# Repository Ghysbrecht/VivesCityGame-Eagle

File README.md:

# VivesCityGame-Eagle
Eagle projects for the VivesCityGame project. This includes the board and schematic files for both the main board and the led board.

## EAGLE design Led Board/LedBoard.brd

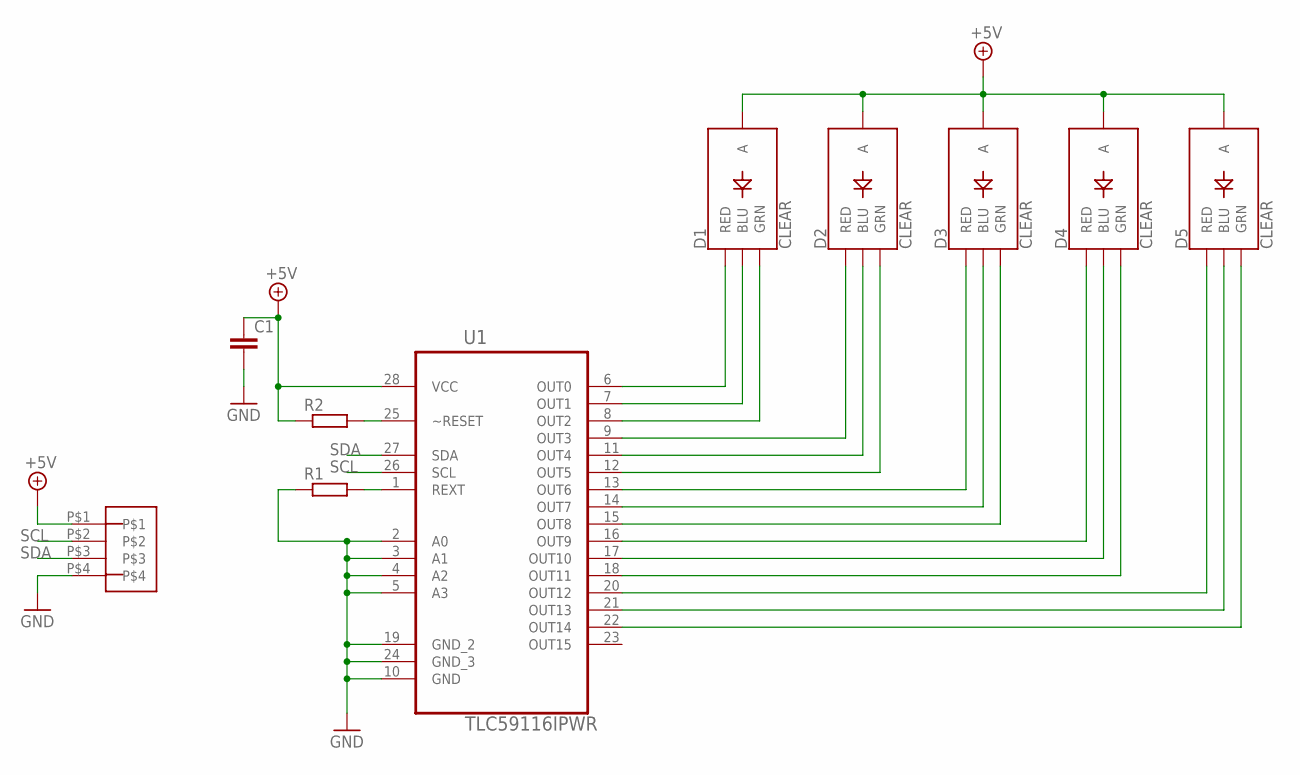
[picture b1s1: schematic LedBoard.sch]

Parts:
C1: C-EUC0603; C0603
D1, D2, D3, D4, D5: CLEAR; LED-RGB-THRU
R1, R2: R-EU_R0603; R0603
U1: TLC59116IPWR; SOP65P640X120-28N
U$1: 4_PIN_JST-XH

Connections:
+5V: C1.1, D1.2 (A), D2.2 (A), D3.2 (A), D4.2 (A), D5.2 (A), R2.1, U1.28 (VCC), U$1.P$1
GND: C1.2, R1.1, U1.2 (A0), U1.3 (A1), U1.4 (A2), U1.5 (A3), U1.10 (GND), U1.19 (GND_2), U1.24 (GND_3), U$1.P$4
unnamed: D1.1 (RED), U1.6 (OUT0)
unnamed: D1.4 (BLU), U1.7 (OUT1)
unnamed: D1.3 (GRN), U1.8 (OUT2)
unnamed: D2.1 (RED), U1.9 (OUT3)
unnamed: D2.4 (BLU), U1.11 (OUT4)
unnamed: D2.3 (GRN), U1.12 (OUT5)
unnamed: D3.1 (RED), U1.13 (OUT6)
unnamed: D3.4 (BLU), U1.14 (OUT7)
unnamed: D3.3 (GRN), U1.15 (OUT8)
unnamed: D4.1 (RED), U1.16 (OUT9)
unnamed: D4.4 (BLU), U1.17 (OUT10)
unnamed: D4.3 (GRN), U1.18 (OUT11)
unnamed: D5.1 (RED), U1.20 (OUT12)
unnamed: D5.4 (BLU), U1.21 (OUT13)
unnamed: D5.3 (GRN), U1.22 (OUT14)
unnamed: R1.2, U1.1 (REXT)
unnamed: R2.2, U1.25 (~RESET)
SCL: U1.26 (SCL), U$1.P$2
SDA: U1.27 (SDA), U$1.P$3

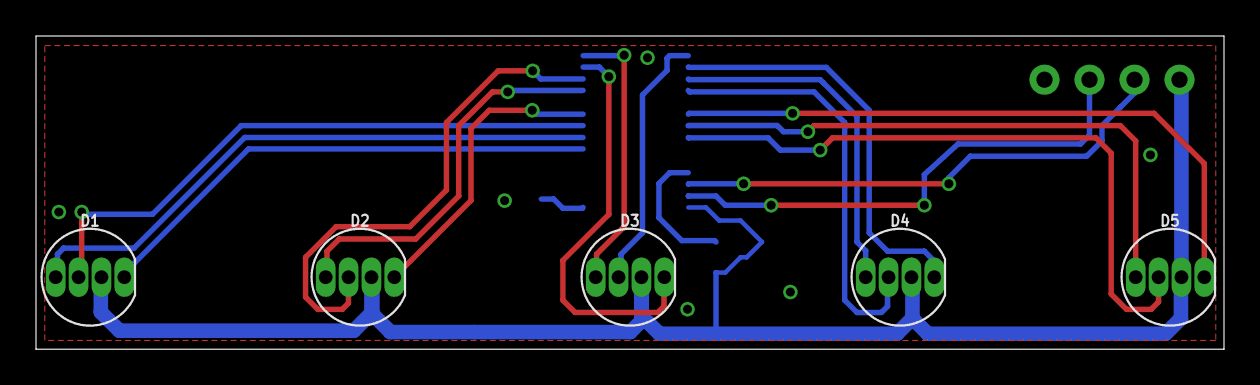
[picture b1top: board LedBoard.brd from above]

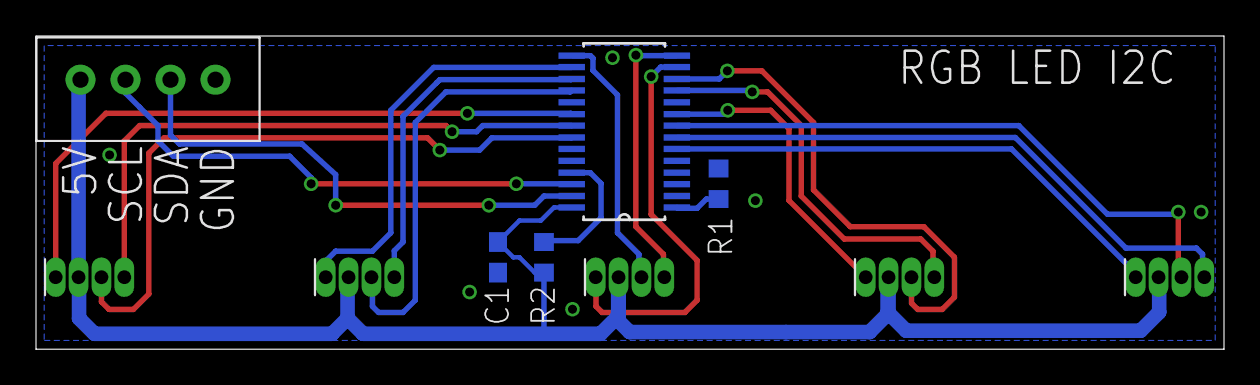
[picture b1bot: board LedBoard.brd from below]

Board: 2 copper layers, 66.0 x 17.4 mm, 10 parts (5 on the bottom side), 21 nets.

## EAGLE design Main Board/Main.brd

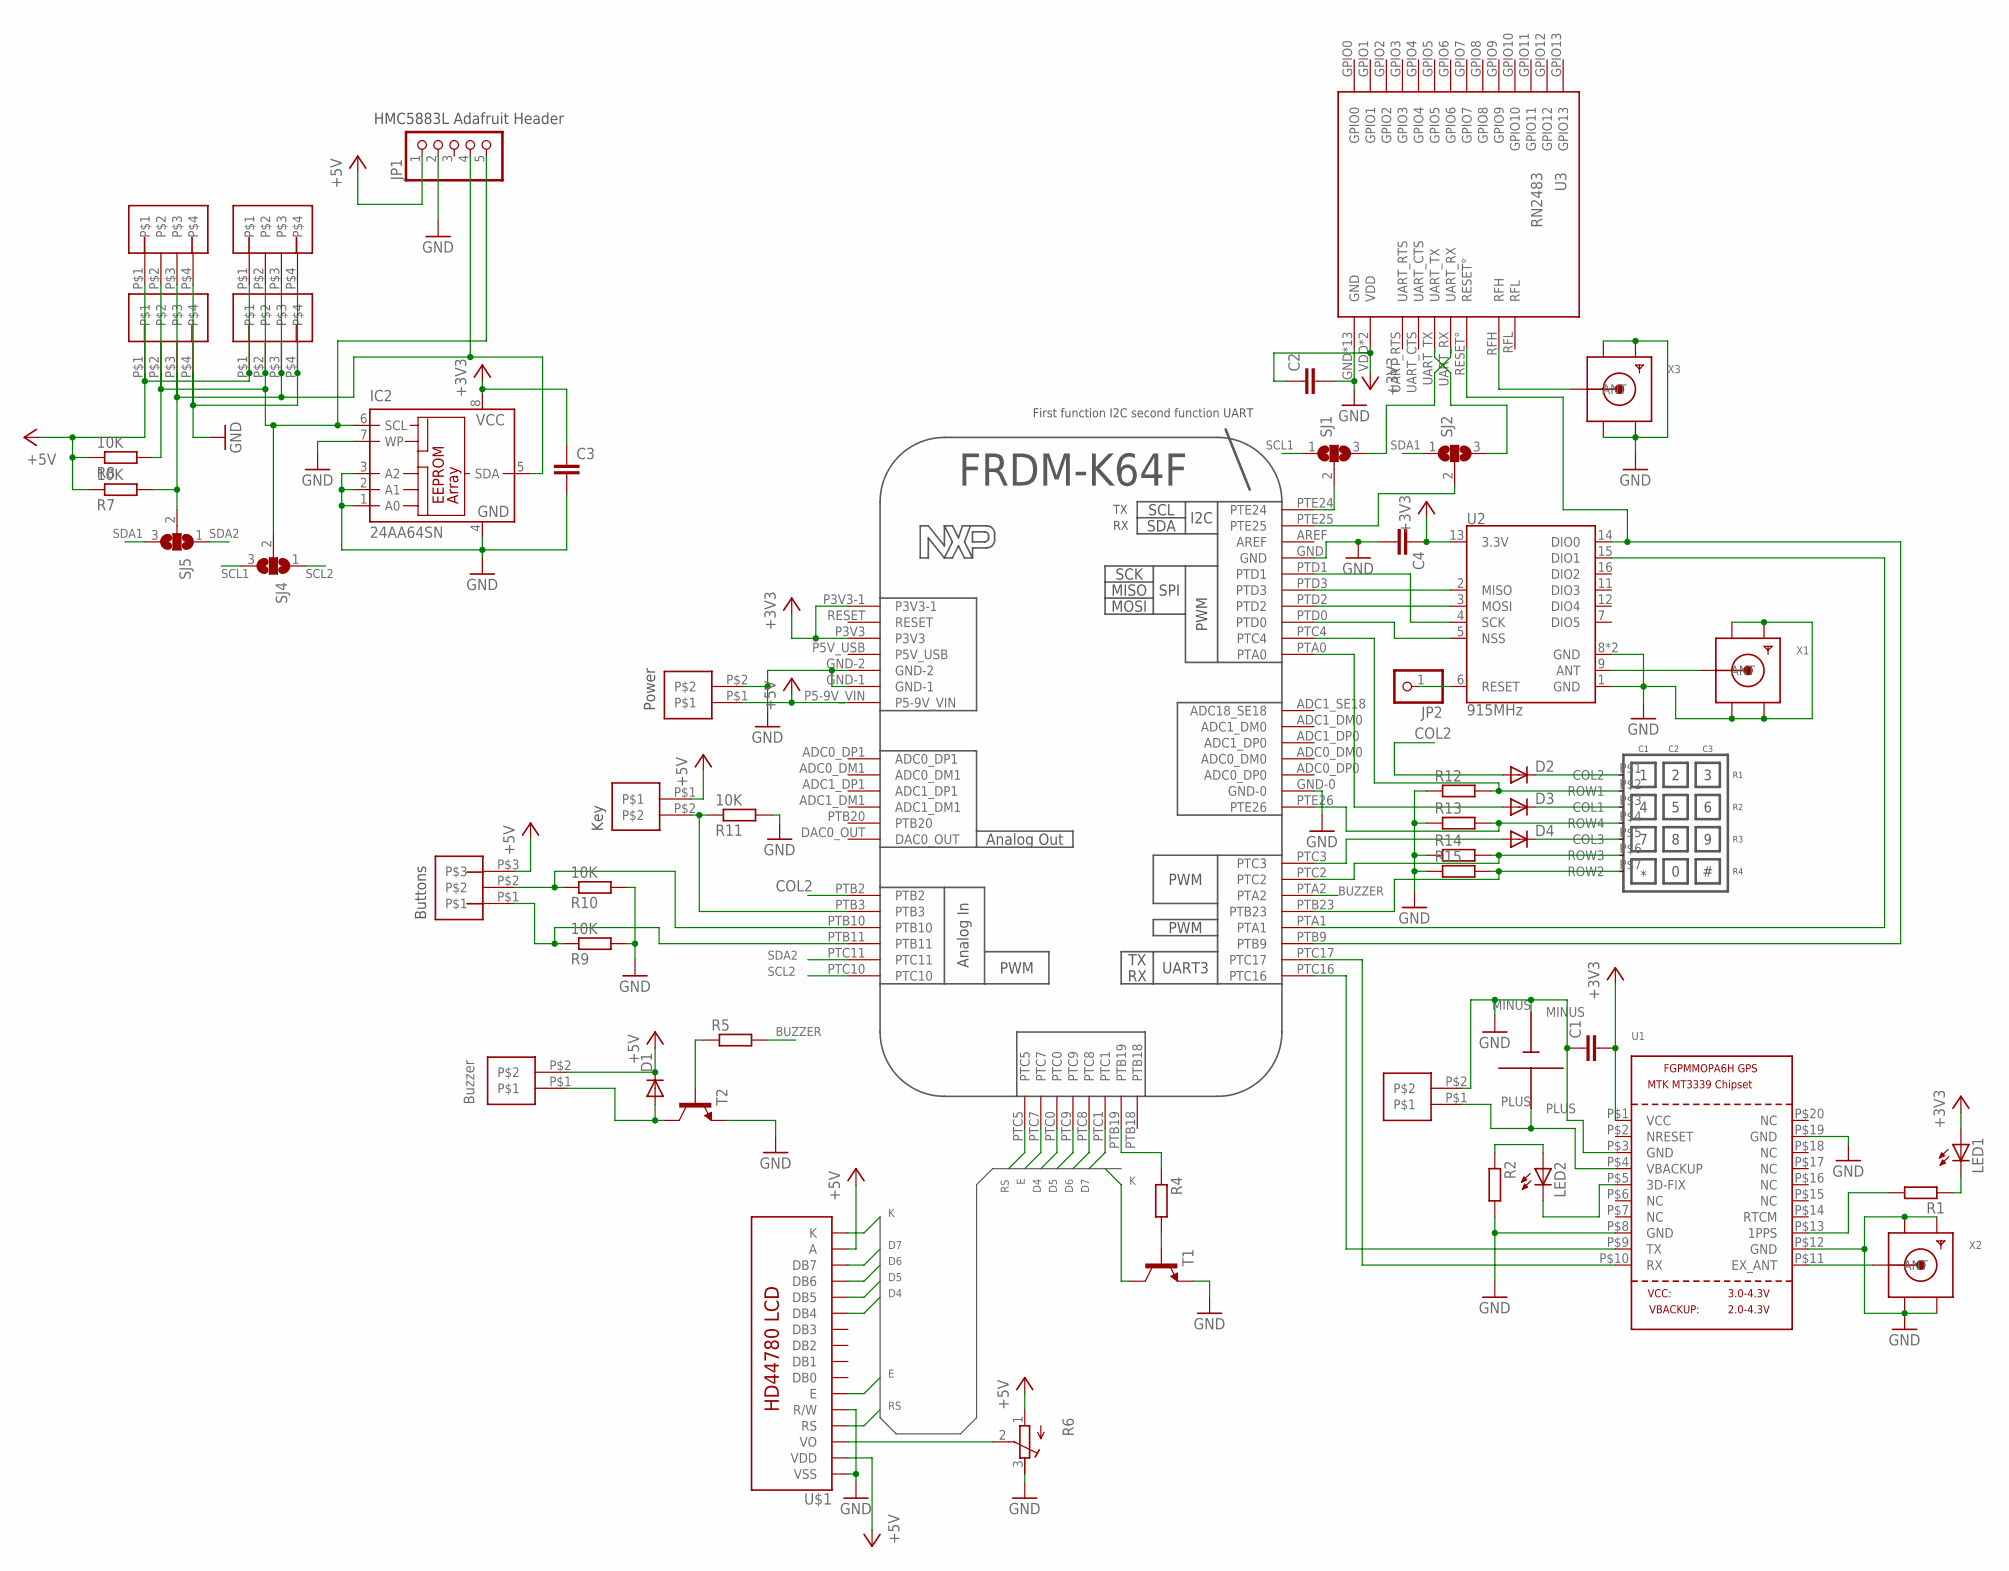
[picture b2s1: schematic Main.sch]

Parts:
C1, C2, C3, C4: C-EUC0603; C0603
D1, D2, D3, D4: DIODE-MINIMELF; MINIMELF
IC2: 24AA64SN; SO-08
JP1: PINHD-1X5; 1X05
JP2: PINHD-1X1; 1X01
LED1, LED2: LEDCHIPLED_1206; CHIPLED_1206
R1, R2, R4, R5, R12, R13, R14, R15: R-EU_R0603; R0603
R6: R-TRIMM3103; RTRIM3103
R7, R8, R9, R10, R11: 10K; R0603
SJ1, SJ2, SJ4, SJ5: SJ2W; SJ_2
T1, T2: MMBT3904LT1-NPN-SOT23-BEC; SOT23-BEC
U1: GPS_FGPMMOPA6H; FGPMMOPA6H
U2: 915MHz; RFM69HCW-XXXS2
U3: RN2483
U$1: LCD-HD447804-HOLES20X4-4HOLES; LCD-20X4-4HOLES
U$2: FRDM
U$3, U$5, U$11, U$12: 4_PIN_JST-XH
U$4, U$8, U$9, U$13: 2_PIN_JST-XH
U$6: 3_PIN_JST-XH
U$10: KEYPAD
U$14: BATTERY-SMD
X1, X2, X3: SMACONNECTOR_EDGE; SMA_EDGELAUNCH

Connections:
+3V3: C1.2, C2.1, C3.1, C4.1, IC2.8 (VCC), LED1.A, U1.P$1 (VCC), U2.13 (3.3V), U3.VDD, U3.VDD2 (VDD), U$2.P3V3, U$2.P3V3-1
+5V: D1.C, JP1.1, R6.1 (E), R7.1, R8.1, U$1.P$2 (VDD), U$1.P$15 (A), U$2.P5-9V_VIN, U$3.P$1, U$4.P$2, U$5.P$1, U$6.P$3, U$8.P$1, U$9.P$1, U$11.P$1, U$12.P$1
BUZZER: R5.2, U$2.PTA2
COL2: D2.A, U$2.PTB2
D4: U$1.P$11 (DB4), U$2.PTC0
D5: U$1.P$12 (DB5), U$2.PTC9
D6: U$1.P$13 (DB6), U$2.PTC8
D7: U$1.P$14 (DB7), U$2.PTC1
E: U$1.P$6 (E), U$2.PTC7
GND: C1.1, C2.2, C3.2, C4.2, IC2.1 (A0), IC2.2 (A1), IC2.3 (A2), IC2.4 (GND), IC2.7 (WP), JP1.2, R2.2, R6.3 (A), R9.2, R10.2, R11.2, R12.1, R13.1, R14.1, R15.1, T1.E, T2.E, U1.P$3 (GND), U1.P$8 (GND), U1.P$12 (GND), U1.P$19 (GND), U2.1 (GND), U2.8 (GND), U2.10 (GND), U3.GND, U3.GND1 (GND), U3.GND2 (GND), U3.GND3 (GND), U3.GND4 (GND), U3.GND5 (GND), U3.GND6 (GND), U3.GND7 (GND), U3.GND8 (GND), U3.GND9 (GND), U3.GND10 (GND), U3.GND11 (GND), U3.GND12 (GND), U$1.P$1 (VSS), U$1.P$5 (R/W), U$2.GND, U$2.GND-0, U$2.GND-1, U$2.GND-2, U$3.P$4, U$5.P$4, U$9.P$2, U$11.P$4, U$12.P$4, U$13.P$2, U$14.MINUS, X1.GND@1 (GND4), X1.GND@2 (GND3), X1.GND@3 (GND2), X1.GND@4 (GND1), X2.GND@1 (GND4), X2.GND@2 (GND3), X2.GND@3 (GND2), X2.GND@4 (GND1), X3.GND@1 (GND4), X3.GND@2 (GND3), X3.GND@3 (GND2), X3.GND@4 (GND1)
K: T1.C, U$1.P$16 (K)
unnamed: U2.2 (MISO), U$2.PTD3
unnamed: U2.3 (MOSI), U$2.PTD2
unnamed: U2.4 (SCK), U$2.PTD1
unnamed: U2.5 (NSS), U$2.PTD0
unnamed: U2.9 (ANT), X1.P (ANT)
unnamed: U1.P$9 (TX), U$2.PTC16
unnamed: U1.P$11 (EX_ANT), X2.P (ANT)
unnamed: D4.C, U$10.P$5 (COL3)
unnamed: U1.P$10 (RX), U$2.PTC17
unnamed: LED1.C, R1.1
unnamed: LED2.A, R2.1
unnamed: LED2.C, U1.P$5 (3D-FIX)
unnamed: R1.2, U1.P$13 (1PPS)
unnamed: SJ1.2, U$2.PTE24
unnamed: R11.1, U$2.PTB3, U$8.P$2
unnamed: U2.14 (DIO0), U3.RESET°, U$2.PTB9
unnamed: U2.15 (DIO1), U$2.PTA1
unnamed: D3.C, U$10.P$3 (COL1)
unnamed: R4.1, U$2.PTB19
unnamed: R4.2, T1.B
unnamed: D1.A, T2.C, U$4.P$1
unnamed: R5.1, T2.B
unnamed: D3.A, U$2.PTA0
unnamed: SJ1.3, U3.UART_RX
unnamed: IC2.5 (SDA), JP1.4, R7.2, SJ5.2, U$3.P$3, U$5.P$3, U$11.P$3, U$12.P$3
unnamed: U1.P$4 (VBACKUP), U$13.P$1, U$14.PLUS
unnamed: D2.C, U$10.P$1 (COL2)
unnamed: R10.1, U$2.PTB10, U$6.P$2
unnamed: R9.1, U$2.PTB11, U$6.P$1
unnamed: R15.2, U$2.PTB23, U$10.P$7 (ROW2)
unnamed: R14.2, U$2.PTC2, U$10.P$6 (ROW3)
unnamed: R13.2, U$2.PTE26, U$10.P$4 (ROW4)
unnamed: R12.2, U$2.PTC4, U$10.P$2 (ROW1)
unnamed: D4.A, U$2.PTC3
unnamed: JP2.1, U2.6 (RESET)
unnamed: SJ2.2, U$2.PTE25
unnamed: SJ2.3, U3.UART_TX
unnamed: IC2.6 (SCL), JP1.5, R8.2, SJ4.2, U$3.P$2, U$5.P$2, U$11.P$2, U$12.P$2
unnamed: U3.RFH, X3.P (ANT)
unnamed: R6.2 (S), U$1.P$3 (VO)
RS: U$1.P$4 (RS), U$2.PTC5
SCL1: SJ1.1, SJ4.3
SCL2: SJ4.1, U$2.PTC10
SDA1: SJ2.1, SJ5.3
SDA2: SJ5.1, U$2.PTC11

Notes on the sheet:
Buzzer
Buttons
Power
Key
First function I2C second function UART
HMC5883L Adafruit Header

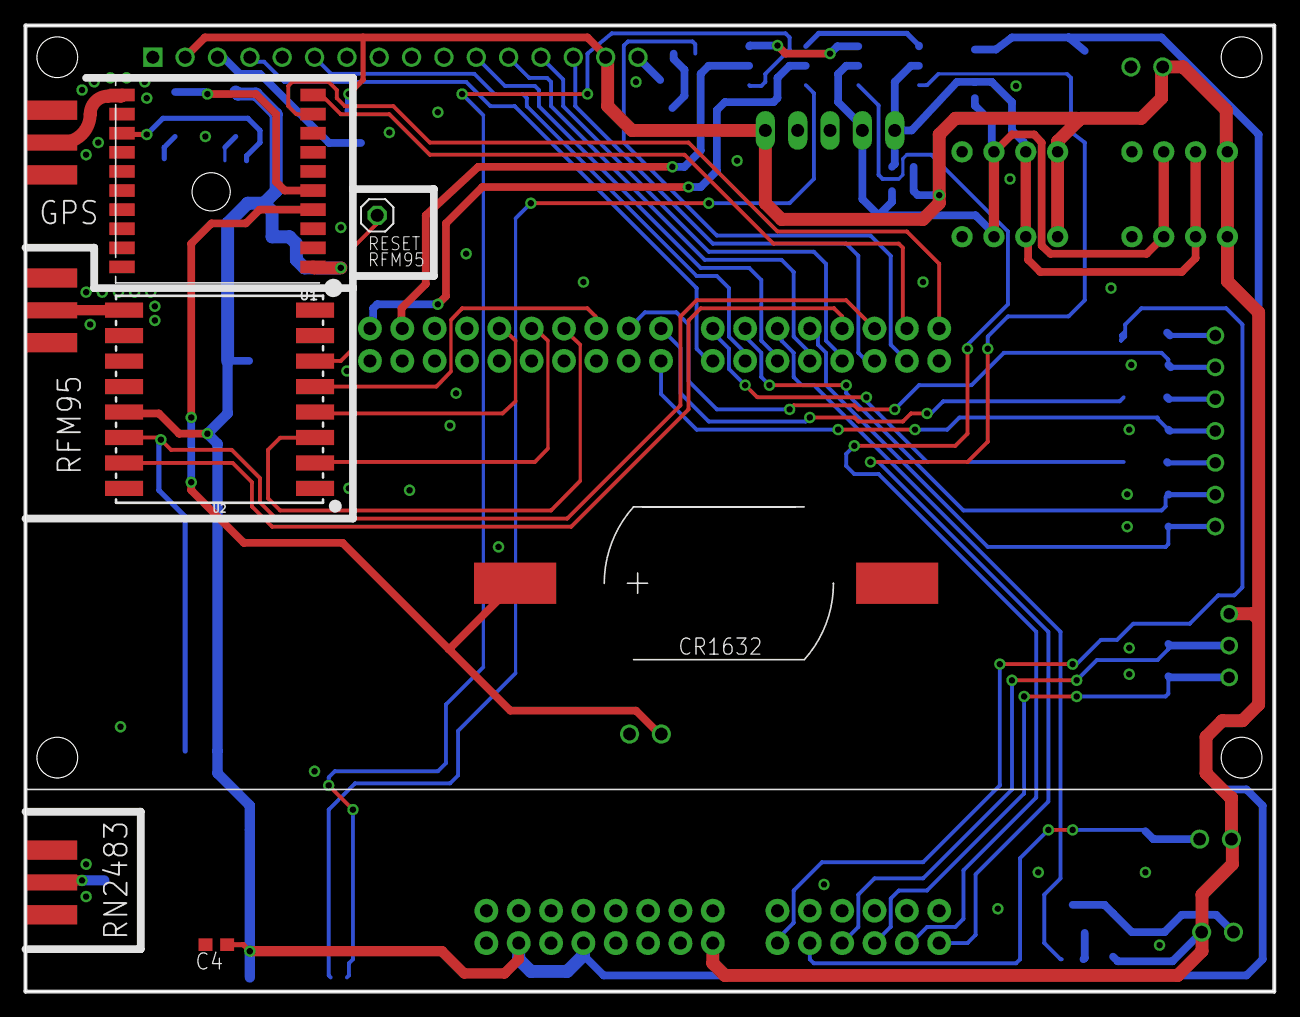
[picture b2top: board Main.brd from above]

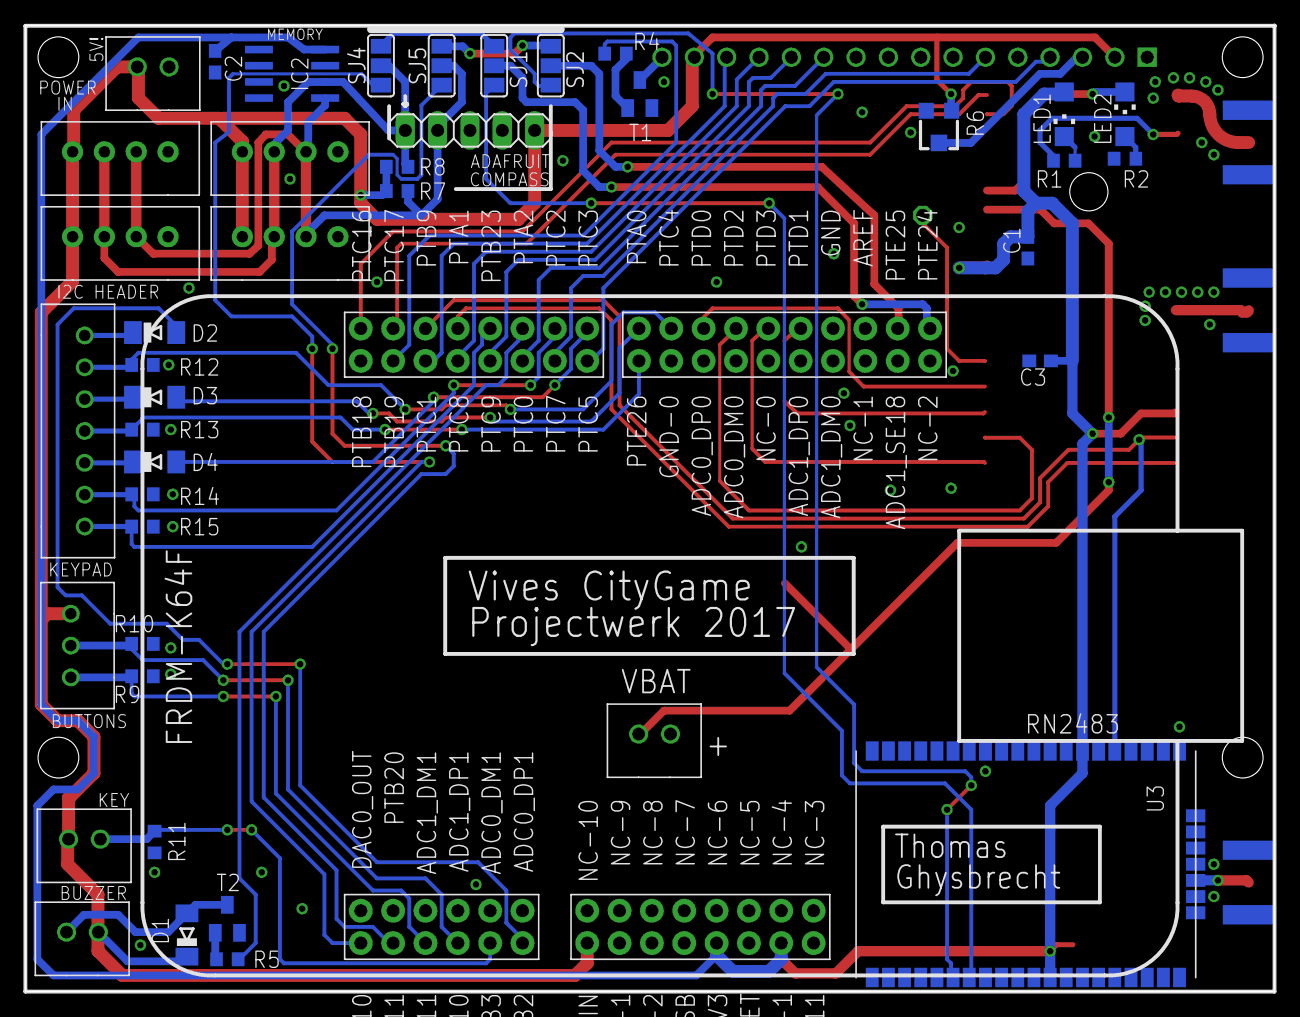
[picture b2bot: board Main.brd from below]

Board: 2 copper layers, 98.1 x 75.9 mm, 52 parts (43 on the bottom side), 56 nets.

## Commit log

2017-05-20 Added the files

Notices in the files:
parts and their libraries:
SparkFun-LED: Licensing: Creative Commons ShareAlike 4.0 International - https://creativecommons.org/licenses/by-sa/4.0
